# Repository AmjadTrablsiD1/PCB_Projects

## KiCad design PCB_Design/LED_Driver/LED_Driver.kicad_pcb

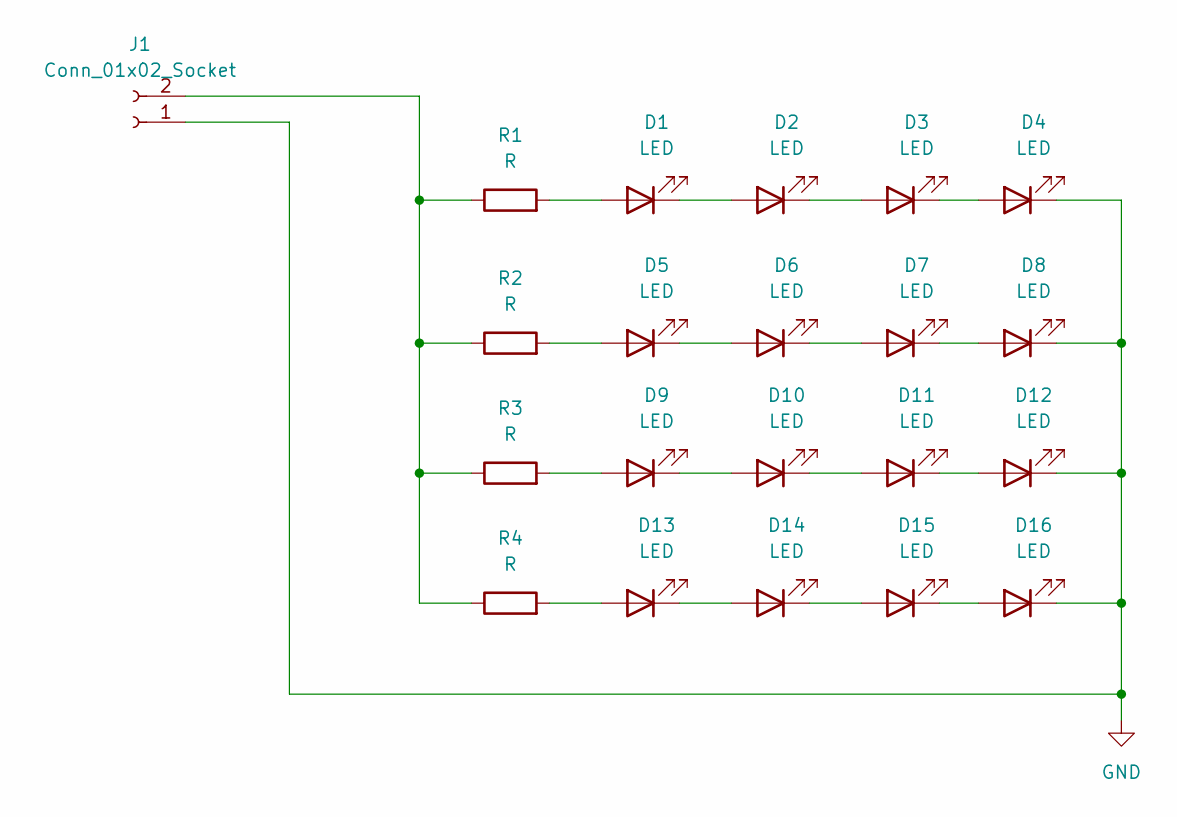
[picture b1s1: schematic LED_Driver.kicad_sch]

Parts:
D1, D2, D3, D4, D5, D6, D7, D8, D9, D10, D11, D12, D13, D14, D15, D16: LED; LED_1W_3W_R8
J1: Conn_01x02_Socket; PinSocket_1x02_P2.54mm_Vertical
R1, R2, R3, R4: R; R_1206_3216Metric_Pad1.30x1.75mm_HandSolder

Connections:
GND: D4.1 (K), D8.1 (K), D12.1 (K), D16.1 (K), J1.1
unnamed: D1.2 (A), R1.2
unnamed: D1.1 (K), D2.2 (A)
unnamed: D2.1 (K), D3.2 (A)
unnamed: D3.1 (K), D4.2 (A)
unnamed: D5.2 (A), R2.2
unnamed: D5.1 (K), D6.2 (A)
unnamed: D6.1 (K), D7.2 (A)
unnamed: D7.1 (K), D8.2 (A)
unnamed: D9.2 (A), R3.2
unnamed: D9.1 (K), D10.2 (A)
unnamed: D10.1 (K), D11.2 (A)
unnamed: D11.1 (K), D12.2 (A)
unnamed: D13.2 (A), R4.2
unnamed: D13.1 (K), D14.2 (A)
unnamed: D14.1 (K), D15.2 (A)
unnamed: D15.1 (K), D16.2 (A)
unnamed: J1.2, R1.1, R2.1, R3.1, R4.1

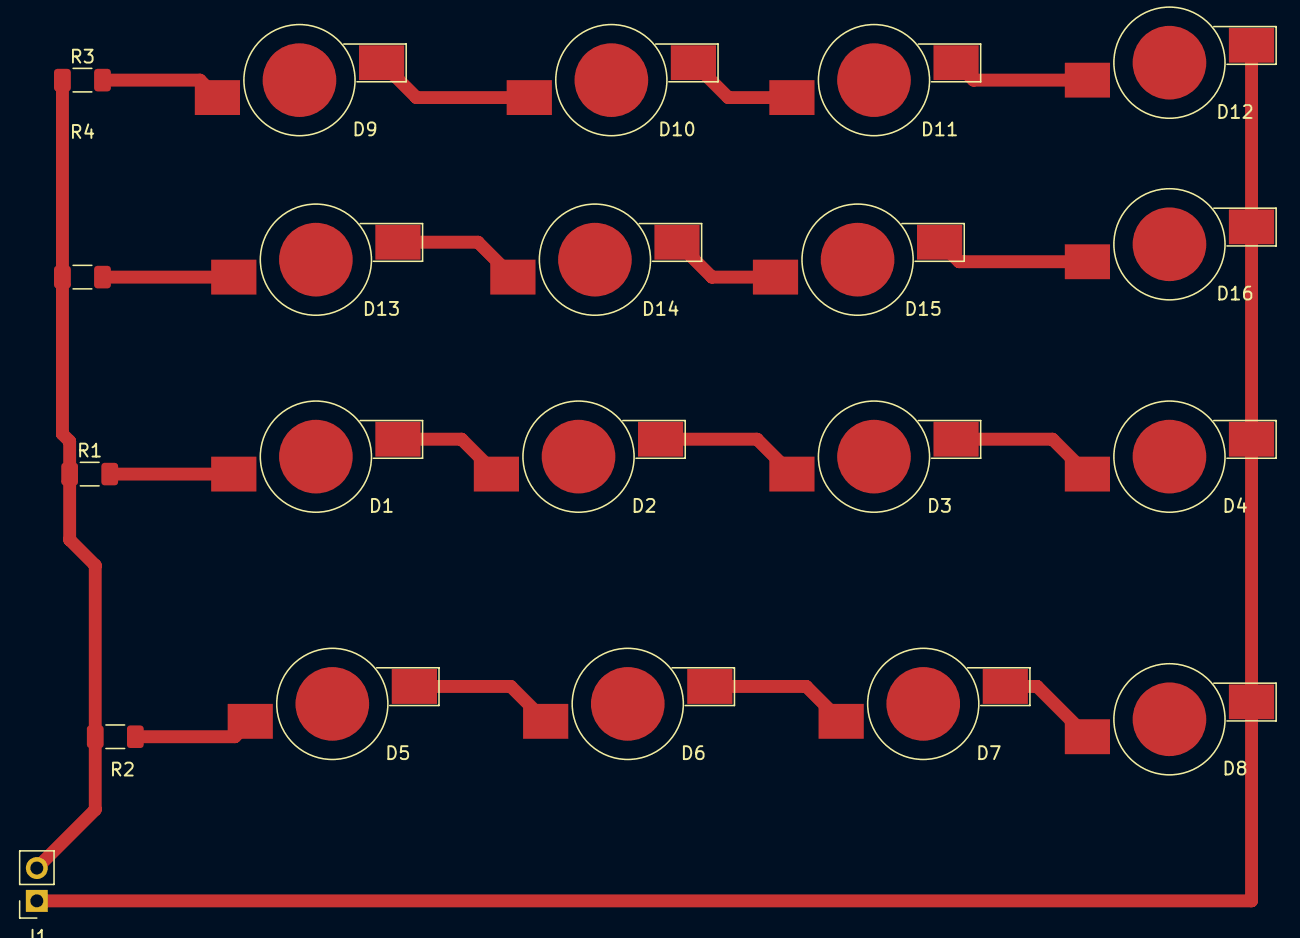
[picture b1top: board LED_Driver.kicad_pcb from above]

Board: 2 copper layers, 21 parts (0 on the bottom side), 18 nets.
